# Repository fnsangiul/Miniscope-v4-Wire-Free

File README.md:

# Miniscope-v4-Wire-Free

The Miniscope v4 Wire-Free is an open-source one photon miniatirized microscope for neural recordings in freely behaving animals.  

This microscope is based on the Miniscope v4, sharing the same optical properties with redesigned electronics. This repository contains the KiCAD project files for the electronics, the complete microcontroller project and the Jupyter notebooks used to set the recording parameters and recover the data from the SD card.

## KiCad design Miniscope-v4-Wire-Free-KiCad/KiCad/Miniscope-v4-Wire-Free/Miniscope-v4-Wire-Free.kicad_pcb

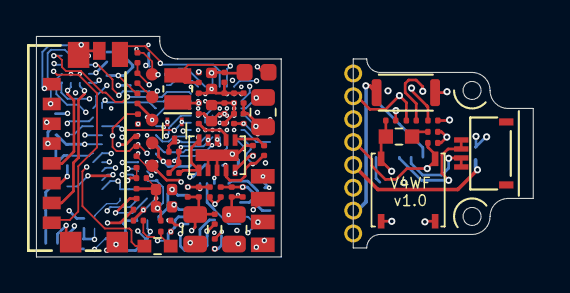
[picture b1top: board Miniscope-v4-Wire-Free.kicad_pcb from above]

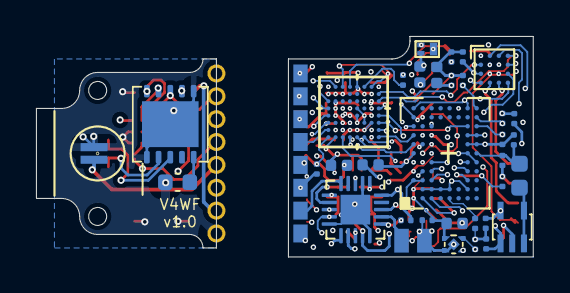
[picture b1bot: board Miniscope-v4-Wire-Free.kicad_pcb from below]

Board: 6 copper layers, 13.6 x 12.2 mm, 115 parts (44 on the bottom side), 83 nets.

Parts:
C1, C2, C6, C7, C26, C35, C50, C51, C52: 10uF; C_0402_1005Metric_L
C3, C4: 10pF; C_0201_0603Metric_L
C5, C11, C12, C13, C15: 2.2uF; C_0201_0603Metric_L
C9, C10, C19, C22, C23, C24, C25, C27, C28, C30, C38, C40, C41, C42, C43, C44, C45, C46, C47, C48, C49, C53: 0.1uF; C_0201_0603Metric_L
C14, C37: 1uF; C_0201_0603Metric_L
C16: 4.7nF 100V; C_0603_1608Metric_L
C17, C29, C36: 4.7uF; C_0201_0603Metric_L
C18, C20: 22pF; C_0201_0603Metric_L
D1: LXZ1-PB01; LED_LXZ1_PR01_L
D2, D3: LED_Small_ALT; LED_SC80X160X65L40L
J1: 0475710001
J2: Conn_01x04; 1x4_USB
J3: Conn_01x04; FH19C-4S-0.5SH(10)
J4, J5, J6, J7, J8, J9, J10, J11, J12, J14, J15, J16, J17, J18, J19, J20, J21, J22, J23, J24, J25, J26, J27: Conn_01x01; Conn_1x1_700_Circular_Pad
L1, L5: 10uH; C_0805_2012Metric_L
L2: 4.7uH; C_0805_2012Metric_L
L3, L4: BLM18PG471SN1D; L_0603_1608Metric_L
Q1: NTK3134NT1G; TRXSOFL3P40_120X120X55L29X21L
Q2: MMBT3904LP-7B; TRXDFN3_101X61X53L25X15N
R1, R17: 25K; R_0201_0603Metric_ERJ_L
R2, R18: R_Small_US; R_0201_0603Metric_ERJ_L
R3: 1.25M; R_0201_0603Metric_ERJ_L
R4: 2.05M; R_0201_0603Metric_ERJ_L
R5: 1M; R_0201_0603Metric_ERJ_L
R6: 649K; R_0201_0603Metric_ERJ_L
R7, R8: 2.2K; R_0201_0603Metric_ERJ_L
R9: 8.2K; R_0201_0603Metric_ERJ_L
R10: 2K; R_0201_0603Metric_ERJ_L
R11, R19: 1K; R_0201_0603Metric_ERJ_L
R12: DNL; R_0201_0603Metric_ERJ_L
R13: 400K; R_0201_0603Metric_ERJ_L
R14, R16, R20: 100K; R_0201_0603Metric_ERJ_L
R15: 37K; R_0201_0603Metric_ERJ_L
R21: 47k5; R_0201_0603Metric_ERJ_L
R22: 10K; R_0201_0603Metric
SW1: TL3780AF330QG; SMD-Switch-3mmx2mm
U1: LTC3554; QFN-20-1EP_3x3mm_P0.4mm_EP1.65x1.65mm
U2: HV892; SON11P65_400X400X80L40X30T315X255L
U3: LTC3218; SON_11_P50_300X200X80L40X25T239X64L
U4: MAX13030EETE+BGA; BGA-16_1.92x1.92mm_Layout4x4_P0.5mm
U5: TSOP57438TT1; SON_4_P300_395X395X90L55X35L
U6: ATSAMD51J20A-UUT-EFP
U7: NCP163AMX330TBG; UQFN_MCP1711
U8: NOIP1SN0480A; BGA88CP50_8X11_493X613X75B25
U9: LMV321IDCKR; SOT_23-5P65_210X110L36X22L
Y2: Crystal; Crystal_SMD_MicroCrystal_CC8V-T1A-2Pin_2.0x1.2mm

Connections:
+1V8: C3.1, C6.1, C9.1, C19.1, C22.1, C25.1, C27.1, C28.1, C35.1, C43.1, C46.1, C49.1, C52.1, J6.1, J19.1, J26.1, L1.2, L3.1, R3.1, R7.1, R8.1, R11.1, R12.1, R16.1, R20.2, R22.1, U1.9 (PWR_ON1), U2.5 (VDD), U4.C1 (VL), U4.C4 (EN), U6.B5 (VDDIO), U6.C3 (VDDIO), U6.E3 (VDDIO), U6.E4 (VDDIOB), U8.A2 (VDD_18), U8.A10 (VDD_18), U8.H9 (VDD_18), U9.1 (+)
+3V3: C4.1, C7.1, C10.1, C11.1, C12.1, C13.1, C30.1, C38.1, C40.1, C41.1, C44.1, C47.1, C50.1, D3.2 (A), J1.P4 (VDD), J14.1, J21.1, L2.2, R4.1, U2.2 (VIN), U3.10 (VIN), U4.C2 (VCC), U5.5 (Vs), U7.3 (nSHDN), U8.B1 (VDD_33), U8.F11 (VDD_33), U8.G3 (VDD_33), U8.H10 (VDD_33), U8.H11 (VDD_33), U9.5 (V+)
/3V3_EN: U1.8 (PWR_ON2), U6.B1 (PA24)
/ADC0: R13.2, R14.1, U6.C7 (PA02)
/BAT+: J10.1, R13.1, U1.17 (BAT)
/CLK1_OUT: U6.H3 (PB15), U8.G9 (CLK_PLL)
/ENT: U3.4 (ENT), U6.B7 (PB01)
/EWL_1: J3.3, J3.4, U2.8 (OUT1)
/EWL_2: J3.1, J3.2, U2.7 (OUT2)
/I2C_BB_SCL: J15.1, J22.1, R8.2, U2.3 (SCL), U6.A8 (PB02)
/I2C_BB_SDA: J16.1, J23.1, R7.2, U2.4 (SDA), U6.A7 (PB00)
/IR_REC: J17.1, J24.1, R15.1, U5.1 (OUT), U6.A2 (PB22)
/I_LED: D1.A, J18.1, J25.1, U3.3 (I_LED)
/I_SET: R10.1, U3.5 (I_SETT), U3.6 (I_SETF)
/LED_PWM: Q1.1 (G), U6.A6 (PB30)
/LED_STATUS: R19.2, U6.F8 (PB09)
/MONITOR0: U6.G8 (PA07), U8.C1 (MONITOR0)
/PCC_CLK: U6.H1 (PA14), U8.A8 (CLK_OUT)
/PCC_DATA0: U6.G1 (PA16), U8.A9 (DOUT2)
/PCC_DATA1: U6.F1 (PA17), U8.C8 (DOUT3)
/PCC_DATA2: U6.E1 (PA18), U8.B8 (DOUT4)
/PCC_DATA3: U6.E2 (PA19), U8.C7 (DOUT5)
/PCC_DATA4: U6.D2 (PA20), U8.B7 (DOUT6)
/PCC_DATA5: U6.D3 (PA21), U8.A7 (DOUT7)
/PCC_DATA6: U6.C1 (PA22), U8.C6 (DOUT8)
/PCC_DATA7: U6.C2 (PA23), U8.C5 (DOUT9)
/PCC_DEN1: U6.F2 (PA12), U6.G3 (PB14), U8.A5 (FRAME_VALID)
/PCC_DEN2: U6.G2 (PA13), U8.B5 (LINE_VALID)
/PUSH_BUT_MCU: R16.2, U1.3 (PBSTAT), U6.A1 (PA25)
/RESET_N: U6.H4 (PB13), U8.C4 (RESET_N)
/SDMMC1_CK: U4.D4 (IO_VL6), U6.G4 (PB11)
/SDMMC1_CMD: U4.B4 (IO_VL5), U6.H8 (PA08)
/SDMMC1_D0: U4.D1 (IO_VL1), U6.G6 (PA09)
/SDMMC1_D1: U4.B1 (IO_VL2), U6.H7 (PA10)
/SDMMC1_D2: U4.A1 (IO_VL3), U6.G5 (PA11)
/SDMMC1_D3: U4.A4 (IO_VL4), U6.H6 (PB15)
/SD_CLK: J1.P5 (CLK), U4.D3 (IO_VCC6)
/SD_CMD: J1.P3 (CMD), U4.B3 (IO_VCC5)
/SD_DAT0: J1.P7 (DAT0), U4.D2 (IO_VCC1)
/SD_DAT1: J1.P8 (DAT1), U4.B2 (IO_VCC2)
/SD_DAT2: J1.P1 (DAT2), U4.A2 (IO_VCC3)
/SD_DAT3: J1.P2 (CD/DAT3), U4.A3 (IO_VCC4)
/SD_DET: J1.G5 (DET), U6.D8 (PB05)
/SPI1_MISO: U6.G7 (PA06), U8.G4 (MISO)
/SPI1_MOSI: U6.F7 (PA04), U8.G5 (MOSI)
/SPI1_NSS: U6.H5 (PB12), U8.A4 (SS_N)
/SPI1_SCK: U6.F6 (PA05), U8.B4 (SCK)
/SWCLK: J7.1, R11.2, U6.C5 (PA30)
/SWDIO: J4.1, R12.2, U6.D5 (PA31)
/TRIGGER0: U6.H2 (PA15), U8.C3 (TRIGGER0)
/UART_RX: J2.2, U6.D1 (PB17)
/UART_TX: J2.3, U6.D4 (PB16)
/USB_VBUS: C1.1, J2.4, R17.2, U1.20 (V_BUS)
/VDDA: C24.1, C26.1, L3.2, U6.E8 (VDDANA)
/VDDCORE: C23.1, C29.1, L5.1, U6.A4 (VDDCORE)
/VDD_PIX: C42.1, C45.1, C48.1, C51.1, U7.1 (VOUT), U8.A1 (VDD_PIX), U8.B6 (VDD_PIX), U8.B10 (VDD_PIX)
/VREF_BOTPLATE: C36.1, C53.1, L4.2, U8.H6 (VREF_BOTPLATE)
/XIN32: C18.1, U6.B8 (PA00), Y2.1
/XOUT32: C20.1, U6.C8 (PA01), Y2.2
/nCHRG: R20.1, U1.14 (nCHRG), U6.A3 (PB23)
/nON: J20.1, J27.1, SW1.2, U1.5 (nON)
/nRESET: J8.1, R22.2, U6.B4 (*RESET)
GND: C1.2, C2.2, C5.2, C6.2, C7.2, C9.2, C10.2, C11.2, C12.2, C13.2, C14.2, C16.2, C17.2, C18.2, C19.2, C20.2, C22.2, C23.2, C24.2, C25.2, C26.2, C27.2, C28.2, C29.2, C30.2, C35.2, C36.2, C37.2, C38.2, C40.2, C41.2, C42.2, C43.2, C44.2, C45.2, C46.2, C47.2, C48.2, C49.2, C50.2, C51.2, C52.2, C53.2, D1.C, J1.G1 (GND), J1.G2 (GND), J1.G3 (GND), J1.G4 (POL), J1.P6 (VSS), J2.1, J5.1, J9.1, J11.1, J12.1, Q1.2 (S), Q2.2 (E), R1.2, R5.1, R6.1, R14.2, R15.2, R18.1, R21.2, SW1.1, U1.2 (FSEL), U1.10 (STBY), U1.15 (NTC), U1.21 (GND), U2.1 (GND1), U2.6 (GND2), U3.7 (ENF), U3.8 (GND), U3.11 (GND), U4.C3 (GND), U5.6 (GND), U5.8 (GND), U6.B2 (GND), U6.C4 (GND), U6.E5 (GNDANA), U6.F3 (GND), U6.F4 (GND), U7.2 (GND), U7.5 (EP), U8.A3 (TR2), U8.A6 (VSS_COLPC), U8.A11 (VSS_COLPC), U8.B2 (VSS_COLPC), U8.B3 (TR1), U8.C2 (SCAN_EN), U8.D2 (VSS_18), U8.E2 (VSS_33), U8.G2 (VSS_33), U8.G6 (VSS_18), U8.G7 (VSS_18), U8.G8 (VSS_18), U8.G11 (VSS_18), U8.H5 (TEST_ENABLE), U8.H7 (VSS_33), U8.H8 (VSS_33), U9.2 (V-)
unnamed: C14.1, R9.1, R10.2
unnamed: D2.2 (A), R2.1
unnamed: D2.1 (K), Q2.3 (C)
unnamed: D3.1 (K), R18.2
unnamed: Q1.3 (D), R9.2
unnamed: Q2.1 (B), R19.1
unnamed: C3.2, R3.2, R5.2, U1.6 (FB1)
unnamed: C4.2, R4.2, R6.2, U1.7 (FB2)
unnamed: R17.1, U1.1 (HPWR)
unnamed: R1.1, U1.16 (PROG)
unnamed: L1.1, U1.13 (SW1)
unnamed: L2.1, U1.11 (SW2)
unnamed: C16.1, U2.10 (HV)
unnamed: C15.2, U3.9 (CM)
unnamed: C15.1, U3.1 (CP)
unnamed: C17.1, U3.2 (eCPO)
unnamed: L5.2, U6.A5 (VSW)
unnamed: R21.1, U8.E1 (IBIAS_MASTER)
unnamed: L4.1, U9.3 (-), U9.4
VDC: C2.1, C5.1, C37.1, R2.2, U1.12 (BVIN), U1.18 (V_OUT), U7.4 (VIN)

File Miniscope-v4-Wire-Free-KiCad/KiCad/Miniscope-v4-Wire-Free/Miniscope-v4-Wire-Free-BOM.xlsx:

Item | Quantity | Reference(s) | Value | Description | Manufacturer Name | Manufacturer Part Number
1 | 9 | C1, C2, C6, C7, C26, C35, C50, C51, C52 | 10uF | CAP CER 10UF 6.3V X5R 0402 | Murata | GRM155R60J106ME15D
2 | 2 | C3, C4 | 10pF | CAP CER 10PF 50V C0G/NP0 0201 | Murata | GRM0335C1H100FA01J
3 | 5 | C5, C11, C12, C13, C15 | 2.2uF | CAP CER 2.2UF 10V X5R 0201 | Murata | GRM033R61A225KE47D
4 | 22 | C9, C10, C19, C22, C23, C24, C25, C27, C28, C30, C38, C40, C41, C42, C43, C44, 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 | 0.1uF | CAP CER 0.1UF 25V X5R 0201 | Murata | GRM033R61E104KE14J
5 | 2 | C14, C37 | 1uF | CAP CER 1UF 10V X5R 0201 | Murata | GRM033R61A105ME15D
6 | 1 | C16 | 4.7nF 100V | CAP CER 4700PF 100V X7R 0603 | Murata | GCM188R72A472KA37D
7 | 3 | C17, C29, C36 | 4.7uF | CAP CER 4.7UF 6.3V X5R 0201 | Murata | GRM035R60J475ME15D
8 | 2 | C18, C20 | 22pF | CAP CER 22PF 50V C0G/NP0 0201 | Murata | GRM0335C1H220GA01D
9 | 1 | D1 | LXZ1-PB01 | LED LUXEON Z BLUE 470NM SMD | Lumileds | LXZ1-PB01
10 | 2 | D2,D3 | RED LED | LED RED CLEAR THIN 0603 SMD | Lite-On Inc. | LTST-C191KEKT
11 | 1 | J1 | 475710001 | CONN MICRO SD CARD PUSH-PULL R/A | Molex | 475710001
12 | 2 | L1, L5 | 10uH | FIXED IND 10UH 300MA 600MOHM SMD | TDK | MLZ1608N100LT000
13 | 1 | L2 | 4.7uH | FIXED IND 4.7UH 180MA 300MOHM SM | Abracon | ASMCI-0805-4R7M-T
14 | 2 | L3, L4 | BLM18PG471SN1D | FERRITE BEAD 470 OHM 0603 1LN | Murata | BLM18PG471SN1D
15 | 1 | Q1 | NTK3134NT1G | Power MOSFET | ON Semiconductor | NTK3134NT1G
16 | 1 | Q2 | MMBT3904LP-7B | TRANS NPN 40V 0.2A DFN1006-3 | Diodes Incorporated | MMBT3904LP-7B
17 | 2 | R1, R17 | 25K | RES SMD 24.9K OHM 1% 1/20W 0201 | Vishay Dale | CRCW020124K9FNED
18 | 2 | R2, R18 | 1.8K | RES SMD 1.8K OHM 1% 1/20W 0201 | Panasonic | ERJ-1GNF1801C
19 | 1 | R3 | 1.25M | RES 1.27M OHM 1% 1/20W 0201 | Vishay Dale | CRCW02011M27FNED
20 | 1 | R4 | 2.05M | RES 2.05M OHM 1% 1/20W 0201 | Vishay Dale | CRCW02012M05FNED
21 | 1 | R5 | 1M | RES SMD 1M OHM 1% 1/20W 0201 | Vishay Dale | CRCW02011M00FNED
22 | 1 | R6 | 649K | RES SMD 649K OHM 1% 1/20W 0201 | Vishay Dale | CRCW0201649KFNED
23 | 2 | R7, R8 | 2.2K | RES SMD 2.2K OHM 1% 1/20W 0201 | Panasonic | ERJ-1GNF2201C
24 | 1 | R9 | 8.2K | RES SMD 8.2K OHM 1% 1/20W 0201 | Vishay Dale | CRCW02018K20FKED
25 | 1 | R10 | 2K | RES SMD 2K OHM 1% 1/20W 0201 | Vishay Dale | CRCW02012K00FNED
26 | 2 | R11, R19 | 1K | RES SMD 1K OHM 1% 1/20W 0201 | Vishay Dale | CRCW02011K00FKED
27 | 1 | R12 | DNL | DNL | DNL | DNL
28 | 1 | R13 | 400K | RES SMD 402K OHM 1% 1/20W 0201 | Panasonic | ERJ-1GNF4023C
29 | 3 | R14, R16, R20 | 100K | RES SMD 100K OHM 1% 1/20W 0201 | Panasonic | ERJ-1GNF1003C
30 | 1 | R15 | 37K | RES SMD 37.4K OHM 1% 1/20W 0201 | Panasonic | ERJ-1GNF3742C
31 | 1 | R21 | 47k5 | RES SMD 47.5K OHM 1% 1/20W 0201 | Vishay Dale | CRCW020147K5FNED
32 | 1 | R22 | 10K | RES SMD 10K OHM 1% 1/20W 0201 | Vishay Dale | ERJ-1GNF1002C
33 | 1 | SW1 | TL3780AF330QG | SWITCH TACTILE SPST-NO 0.02A 15V | E-Switch | TL3780AF330QG
34 | 1 | U1 | LTC3554 | IC USB POWER MANAGER 20UTQFN | Analog Devices Inc. | LTC3554EUD#PBF
35 | 1 | U2 | HV892 | IC LED DRIVER LENS 10WDFN | Microchip | HV892K7-G
36 | 1 | U3 | LTC3218 | IC LED DRIVER RGLTR 150MA 10DFN | Analog Devices Inc. | LTC3218
37 | 1 | U4 | MAX13030EETE+BGA | IC TRNSLTR BIDIRECTIONAL 16TQFN | Maxim Integrated | MAX13030EETE+
38 | 1 | U5 | TSOP57438TT1 | SENSOR REMOTE REC 38.0KHZ 40M | Vishay Semiconductor Opto Division | TSOP57438TT1
39 | 1 | U6 | ATSAMD51J20A-UUT-EFP | MCU 120MHZ 1024KB FLASH 64 | Microchip | ATSAMD51J20A-UUT-EFP
40 | 1 | U7 | NCP163AMX330TBG | IC REG LINEAR 3.3V 250MA 4XDFN | onsemi | NCP163AMX330TBG
41 | 1 | U8 | NOIP1SN0480A | IC CMOS IMAGE SENSOR 1/3.6" | onsemi | NOIP1SN0480A-STI1
42 | 1 | U9 | LMV321IDCKR | IC OPAMP GP 1 CIRCUIT SC70-5 | Texas Instruments | LMV321IDCKR
43 | 1 | J3 | FH19C-4S-0.5SH | CONN FFC BOTTOM 4POS 0.5MM R/A | Hirose | FH19C-4S-0.5SH(10)
44 | 1 | Y2 | Crystal | CRYSTAL 32.7680KHZ 12.5PF SMD | TXC CORPORATION | 9HT11-32.768KBZF-T
Total | 91

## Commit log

2023-08-05 Updates to the jupyter notebooks
    - Added capability to recover the timestamps from the recording and generate a comma separated value file
    - Added the pullup resistor to the reset line of the MCU in the PCB.
    - Added the gerbers used for the batch fabrication
2025-01-04 Added new gerbers for the fabrication outputs for version 1.0
    - Generated new fabrication outputs for the v1.0
    - Corrected the resistor value for the reset pull up resistor (from 1k to 10k)

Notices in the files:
parts and their libraries:
Copyright 2016 Accelerated Designs. All rights reserved.
